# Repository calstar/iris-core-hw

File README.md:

View this project on [CADLAB.io](https://cadlab.io/project/23494). 

# iris-core-hw

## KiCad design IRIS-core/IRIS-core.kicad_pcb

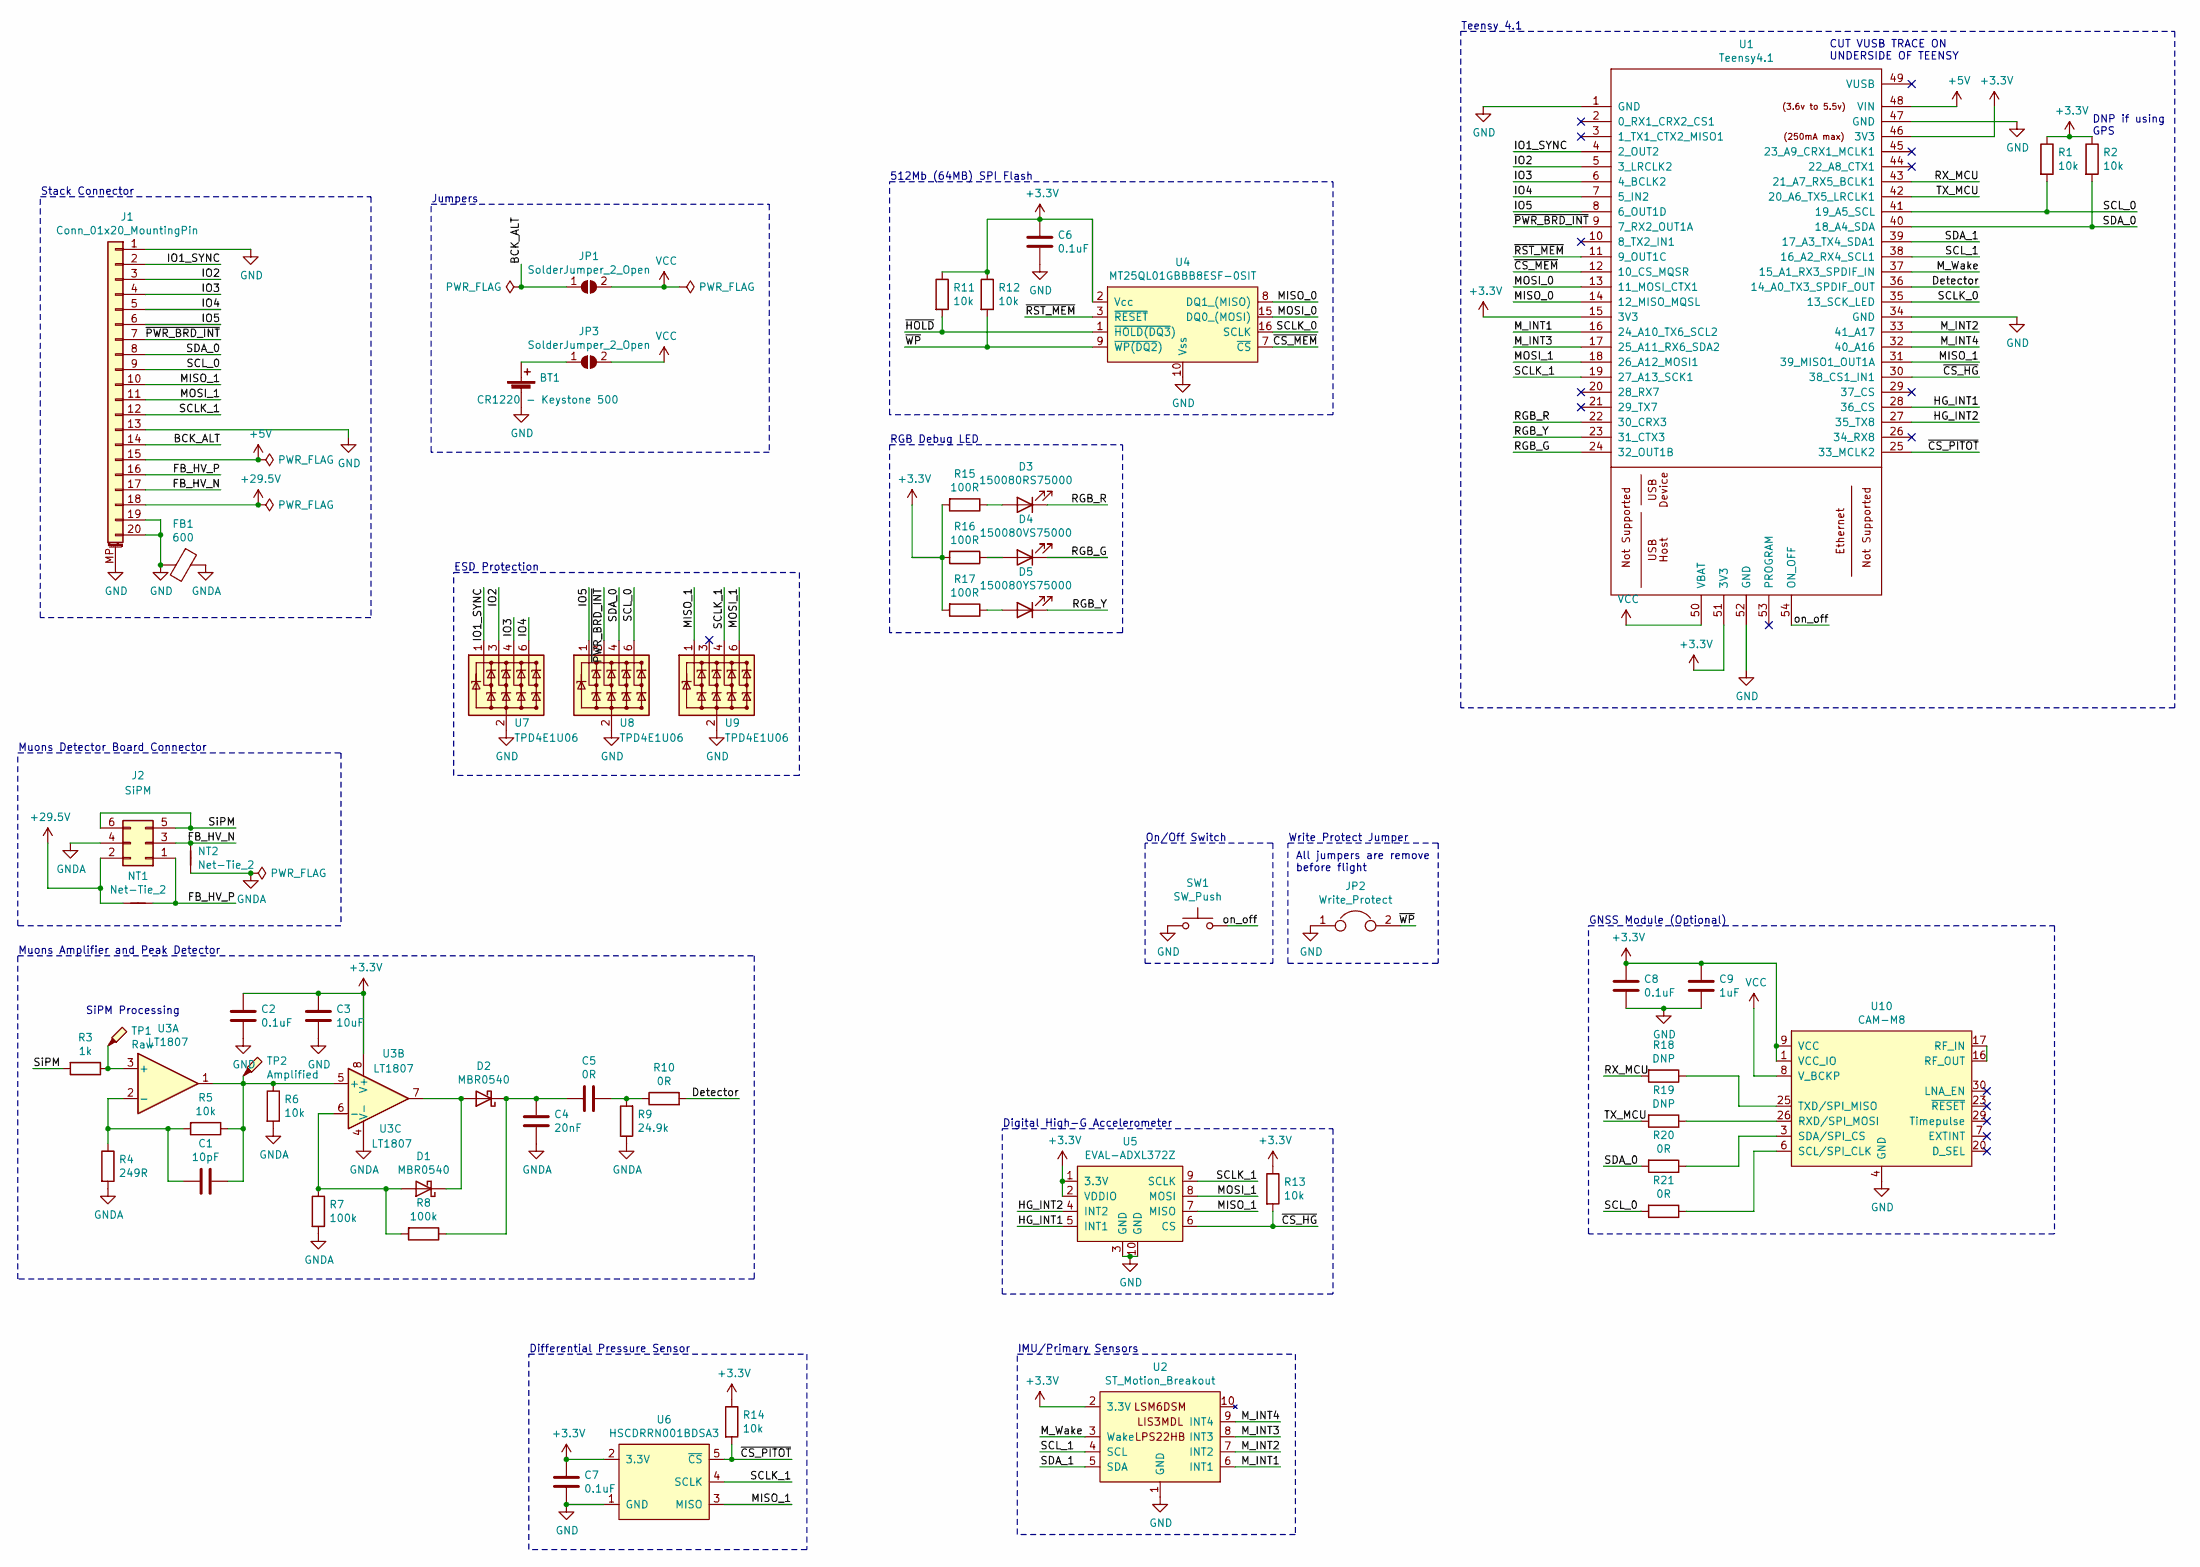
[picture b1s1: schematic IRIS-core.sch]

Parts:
BT1: CR1220 - Keystone 500; CR12XX-Keystone-500; Digikey P/N 36-500-ND
C1: 10pF; C_0603_1608Metric; Digikey P/N 1276-1069-1-ND
C2, C6, C7, C8: 0.1uF; C_0603_1608Metric; Digikey P/N 1276-CL10B104KB8NNNLCT-ND
C3: 10uF; C_0603_1608Metric; Digikey P/N 1276-1192-1-ND
C4: 20nF; C_0805_2012Metric; Digikey P/N 478-10428-1-ND
C5: 0R; C_0603_1608Metric; Digikey P/N RMCF0603ZT0R00CT-ND
C9: 1uF; C_0603_1608Metric; Digikey P/N 1276-1102-1-ND
D1, D2: MBR0540; D_SOD-123; Digikey P/N MBR0540T3GOSCT-ND
D3: 150080RS75000; LED_0805_2012Metric_Pad1.15x1.40mm_HandSolder; Digikey P/N 732-4984-1-ND
D4: 150080VS75000; LED_0805_2012Metric_Pad1.15x1.40mm_HandSolder; Digikey P/N 732-4986-1-ND
D5: 150080YS75000; LED_0805_2012Metric_Pad1.15x1.40mm_HandSolder; Digikey P/N 732-4987-1-ND
FB1: 600; L_0603_1608Metric; Digikey P/N 732-1593-1-ND
J1: Conn_01x20_MountingPin; IRIS_Muons_physical
J2: SiPM
JP1, JP3: SolderJumper_2_Open; SolderJumper-2_P1.3mm_Open_RoundedPad1.0x1.5mm
JP2: Write_Protect; PinHeader_1x02_P2.54mm_Horizontal; Digikey P/N 2057-PH1RB-02-UA-ND
NT1, NT2: Net-Tie_2; NetTie-2_SMD_Pad0.5mm
R1, R2, R5, R6, R11, R12, R13, R14: 10k; R_0603_1608Metric; Digikey P/N RNCP0603FTD10K0CT-ND
R3: 1k; R_0603_1608Metric; Digikey P/N RMCF0603FT1K00CT-ND
R4: 249R; R_0603_1608Metric; Digikey P/N P249BLCT-ND
R7, R8: 100k; R_0603_1608Metric; Digikey P/N RR08P100KDCT-ND
R9: 24.9k; R_0603_1608Metric; Digikey P/N RR08P24.9KDCT-ND
R10, R20, R21: 0R; R_0603_1608Metric; Digikey P/N RMCF0603ZT0R00CT-ND
R15, R16, R17: 100R; R_0603_1608Metric; Digikey P/N RMCF0603FT100RCT-ND
R18, R19: DNP; R_0603_1608Metric
SW1: SW_Push; SW_Tactile_SPST_Angled_PTS645Vx39-2LFS; Digikey P/N CKN9103-ND
TP1: Raw; TestPoint_Keystone_5005-5009_Compact; Digikey P/N 36-5006-ND
TP2: Amplified; TestPoint_Keystone_5005-5009_Compact; Digikey P/N 36-5006-ND
U1: Teensy4.1; Teensy41
U2: ST_Motion_Breakout
U3: LT1807; SOIC-8_3.9x4.9mm_P1.27mm; Digikey P/N LT1807IS8#TRPBFCT-ND
U4: MT25QL01GBBB8ESF-0SIT; SOIC-16W_7.5x10.3mm_P1.27mm; Digikey P/N 557-1789-ND
U5: EVAL-ADXL372Z; Digikey P/N 1127-3597-ND
U6: HSCDRRN001BDSA3
U7, U8, U9: TPD4E1U06; SOT-23-6; Digikey P/N 296-35965-1-ND
U10: CAM-M8; UBLOX_CAM_M8; Digikey P/N 672-CAM-M8Q-0TR-ND

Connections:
+3V3: C2.1, C3.1, C6.1, C7.1, C8.1, C9.1, R1.1, R2.1, R11.1, R12.1, R13.1, R14.1, R15.2, R16.2, R17.2, U1.15 (3V3), U1.46 (3V3), U1.51 (3V3), U2.2 (3.3V), U3.8 (V+), U4.2 (Vcc), U5.1 (3.3V), U5.2 (VDDIO), U6.2 (3.3V), U10.1 (VCC_IO), U10.9 (VCC)
+5V: J1.15, U1.48 (VIN)
+29.5V: J1.18, J2.2, NT1.2
/BCK_ALT: J1.14, JP1.1 (A)
/Detector: R10.2, U1.36 (14_A0_TX3_SPDIF_OUT)
/FB_HV_N: J1.17, J2.3, NT2.1
/FB_HV_P: J1.16, J2.1, NT1.1
/HG_INT1: U1.28 (36_CS), U5.5 (INT1)
/HG_INT2: U1.27 (35_TX8), U5.4 (INT2)
/IO1_SYNC: J1.2, U1.4 (2_OUT2), U7.1 (IO1)
/IO2: J1.3, U1.5 (3_LRCLK2), U7.3 (IO2)
/IO3: J1.4, U1.6 (4_BCLK2), U7.4 (IO3)
/IO4: J1.5, U1.7 (5_IN2), U7.6 (IO4)
/IO5: J1.6, U1.8 (6_OUT1D), U8.1 (IO1)
/MISO_0: U1.14 (12_MISO_MQSL), U4.8 (DQ1_(MISO))
/MISO_1: J1.10, U1.31 (39_MISO1_OUT1A), U5.7 (MISO), U6.3 (MISO), U9.1 (IO1)
/MOSI_0: U1.13 (11_MOSI_CTX1), U4.15 (DQ0_(MOSI))
/MOSI_1: J1.11, U1.18 (26_A12_MOSI1), U5.8 (MOSI), U9.6 (IO4)
/M_INT1: U1.16 (24_A10_TX6_SCL2), U2.6 (INT1)
/M_INT2: U1.33 (41_A17), U2.7 (INT2)
/M_INT3: U1.17 (25_A11_RX6_SDA2), U2.8 (INT3)
/M_INT4: U1.32 (40_A16), U2.9 (INT4)
/M_Wake: U1.37 (15_A1_RX3_SPDIF_IN), U2.3 (Wake)
/RGB_G: D4.1 (K), U1.24 (32_OUT1B)
/RGB_R: D3.1 (K), U1.22 (30_CRX3)
/RGB_Y: D5.1 (K), U1.23 (31_CTX3)
/RX_MCU: R18.2, U1.43 (21_A7_RX5_BCLK1)
/SCLK_0: U1.35 (13_SCK_LED), U4.16 (SCLK)
/SCLK_1: J1.12, U1.19 (27_A13_SCK1), U5.9 (SCLK), U6.4 (SCLK), U9.4 (IO3)
/SCL_0: J1.9, R1.2, R21.2, U1.41 (19_A5_SCL), U8.6 (IO4)
/SCL_1: U1.38 (16_A2_RX4_SCL1), U2.4 (SCL)
/SDA_0: J1.8, R2.2, R20.2, U1.40 (18_A4_SDA), U8.4 (IO3)
/SDA_1: U1.39 (17_A3_TX4_SDA1), U2.5 (SDA)
/SiPM: J2.5, J2.6, R3.2
/TX_MCU: R19.2, U1.42 (20_A6_TX5_LRCLK1)
/on_off: SW1.2, U1.54 (ON_OFF)
/~CS_HG: R13.2, U1.30 (38_CS1_IN1), U5.6 (CS)
/~CS_MEM: U1.12 (10_CS_MQSR), U4.7 (~CS)
/~CS_PITOT: R14.2, U1.25 (33_MCLK2), U6.5 (~CS)
/~HOLD: R11.2, U4.1 (~HOLD(DQ3))
/~PWR_BRD_INT: J1.7, U1.9 (7_RX2_OUT1A), U8.3 (IO2)
/~RST_MEM: U1.11 (9_OUT1C), U4.3 (~RESET)
/~WP: JP2.2, R12.2, U4.9 (~WP(DQ2))
GND: BT1.2 (-), C2.2, C3.2, C6.2, C7.2, C8.2, C9.2, FB1.2, J1.1, J1.13, J1.19, J1.20, J1.MP (MountPin), JP2.1, SW1.1, U1.1 (GND), U1.34 (GND), U1.47 (GND), U1.52 (GND), U2.1 (GND), U4.10 (Vss), U5.3 (GND), U5.10 (GND), U6.1 (GND), U7.2 (GND), U8.2 (GND), U9.2 (GND), U10.4 (GND), U10.5 (GND), U10.10 (GND), U10.11 (GND), U10.12 (GND), U10.13 (GND), U10.14 (GND), U10.15 (GND), U10.18 (GND), U10.19 (GND), U10.21 (GND), U10.22 (GND), U10.27 (GND), U10.31 (GND)
GNDA: C4.2, FB1.1, J2.4, NT2.2, R4.2, R6.2, R7.2, R9.1, U3.4 (V-)
unnamed: BT1.1 (+), JP3.1 (A)
unnamed: C1.1, R5.1, R6.1, TP2.1, U3.1, U3.5 (+)
unnamed: C1.2, R4.1, R5.2, U3.2 (-)
unnamed: C4.1, C5.2, D2.1 (K), R8.1
unnamed: C5.1, R9.2, R10.1
unnamed: D1.1 (K), D2.2 (A), U3.7
unnamed: D1.2 (A), R7.1, R8.2, U3.6 (-)
unnamed: D3.2 (A), R15.1
unnamed: D4.2 (A), R16.1
unnamed: D5.2 (A), R17.1
unnamed: R3.1, TP1.1, U3.3 (+)
unnamed: R18.1, U10.25 (TXD/SPI_MISO)
unnamed: R19.1, U10.26 (RXD/SPI_MOSI)
unnamed: R20.1, U10.3 (SDA/SPI_CS)
unnamed: R21.1, U10.6 (SCL/SPI_CLK)
unnamed: U10.16 (RF_OUT), U10.17 (RF_IN)
VCC: JP1.2 (B), JP3.2 (B), U1.50 (VBAT), U10.8 (V_BCKP)

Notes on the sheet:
Digital High-G Accelerometer
512Mb (64MB) SPI Flash
IMU/Primary Sensors
RGB Debug LED
SiPM Processing
CUT VUSB TRACE ON UNDERSIDE OF TEENSY
All jumpers are remove before flight
DNP if using GPS
Teensy 4.1
GNSS Module (Optional)
Differential Pressure Sensor
Muons Amplifier and Peak Detector
Muons Detector Board Connector
Jumpers
Write Protect Jumper
ESD Protection
On/Off Switch
Stack Connector

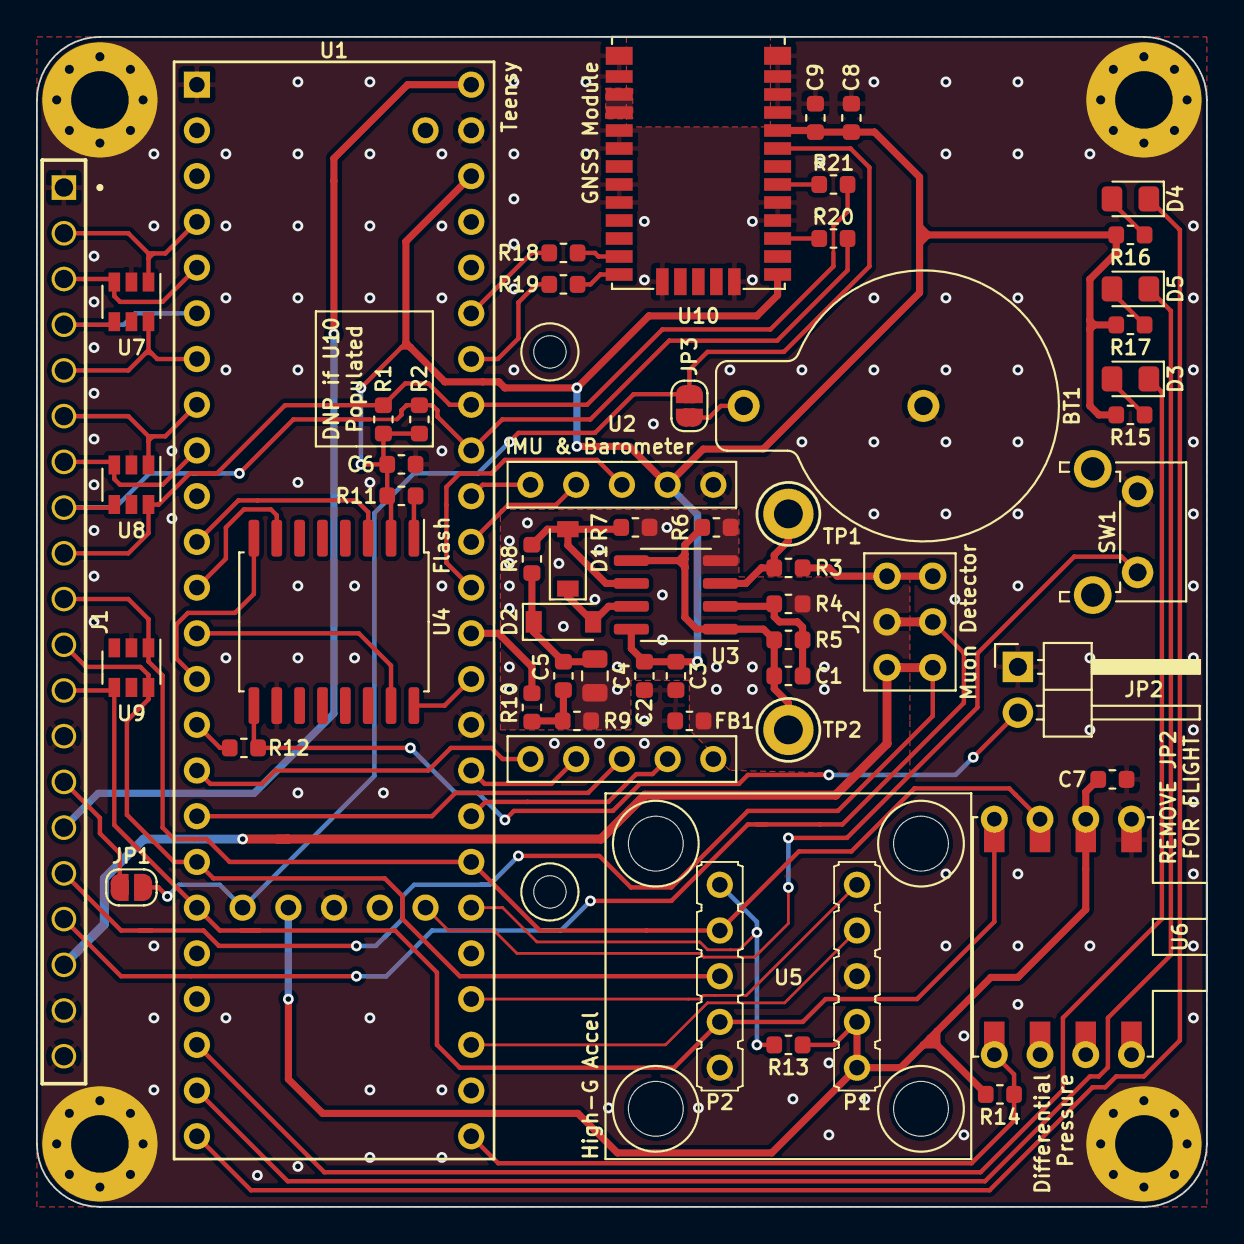
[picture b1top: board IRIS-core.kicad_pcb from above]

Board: 2 copper layers, 65.0 x 65.0 mm, 57 parts (0 on the bottom side), 62 nets.

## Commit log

2020-08-31 Added ESP32
2020-10-13 IRIS Core V4.0 draft
2020-11-06 Added BOM, IRIS core ready for review
2020-11-06 Backlink to CADLAB.io has been added.
2021-01-27 IRIS Core
